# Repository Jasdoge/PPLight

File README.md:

# Usage:

1. The lamp automatically turns on when you move it
2. The lamp starts fading out after being still for 30 seconds, fully turning off after another 30 seconds.

## Charging:

1. Plug it to a 5V USB outlet with a Type-C cable.
2. The battery only charges at 100mA, so even a computer port will be able to charge it.
3. While charging, the lights will fade in and out with a pause between.
4. When fully charged, the lights will turn off.
5. A fully discharged battery reaches 90%+ charge in 2 hours.

## Troubleshooting:

1. After charging, you may need to led the device be still for a few seconds before it can turn on again.
2. If the device still won't turn on, you may need to reset it (this should be exceedingly rare though, and I didn't manage to reproduce it myself after setting the proper BOD). To reset it, open the case by removing the lid (but be careful since the silk filament is a little brittle), and use a fork or knife to briefly short the BAT1 solder joints.

# 3d printing

The 3d print files are located in the Prints director. It's designed for a multi material printer where you want to combine the lid and logo into one mesh, giving the logo priority.

# Schematics

Schematics are located within the Kicad directory.

# Reprogramming

If you want to reprogram your light you'll need the following:

- An arduino (pref arduino UNO)
- A breadboard
- A 10uF electrolytic capacitor
- A 4.7 kOhm resistor.
- 8-pin SOIC test clips. https://www.aliexpress.com/item/33058340727.html

1. Install the MegaTinyCore library in arduino. (If you haven't installed Arduino, do so at https://www.arduino.cc/
2. Then follow the instructions here: https://github.com/SpenceKonde/megaTinyCore/blob/master/MakeUPDIProgrammer.md But **do not connect the power pin to the PPLight**. In the tutorial they use a 470 ohm resistor on the UPDI wire, you can use a 4.7k instead, it doesn't matter that much.
3. Connect pin 6 of your arduino to your breadboard, then to pin 6 of the clips (second from the bottom right, the red wire on the clips is top left).
4. Connect ground to the top right of your test clips.
5. Connect the clips to the attiny on the board. The chamfered edge is left. Align it so the red cable on the clips is top left.
6. Use the following arduino settings:
- Board: ATtiny412/402/212/202
- Chip: ATtiny402
- Clock: 1 MHz internal
- millis()/micros(): Enabled (default timer)
- Support SerialEvent: No
- Port: Port of your arduino
- Programmer: jtag2updi
- The rest don't matter. Don't burn bootloader unless you know what you're doing.
7. You should now be able to upload your code.

**Note: If you're struggling with these instructions, let me know and I'll make a youtube video**

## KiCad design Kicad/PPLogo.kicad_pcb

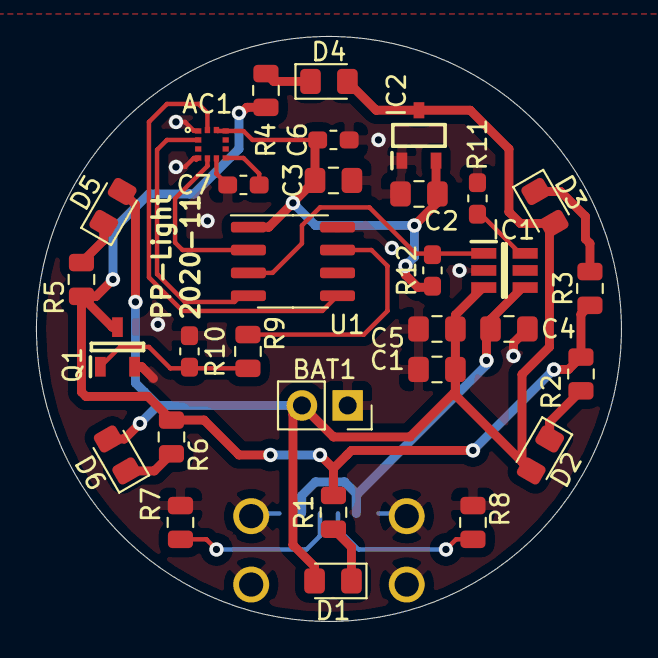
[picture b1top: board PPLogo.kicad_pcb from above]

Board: 2 copper layers, 32.5 x 32.5 mm, 32 parts (1 on the bottom side), 21 nets.

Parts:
AC1: KXTJ3-1057; 2X2X0.9MMLGA
BAT1: BAT; PinSocket_1x02_P2.54mm_Vertical
C1, C2, C3, C4, C5: 10uF; C_0805_2012Metric_Pad1.15x1.40mm_HandSolder
C6, C7: 0.1uF; C_0603_1608Metric_Pad1.05x0.95mm_HandSolder
D1, D2, D3, D4, D5, D6: LED; LED_0805_2012Metric_Pad1.15x1.40mm_HandSolder
IC1: TP4057-42-SOT26-R; SOT95P280X125-6N
IC2: XC6206P332MR; SOT95P280X130-3N
J1: TYPE-C-31-M-17; TYPEC31M17
Q1: JST2302H; SOT95P240X115-3N
R1, R2, R3, R4, R5, R6: 220; R_0805_2012Metric
R7, R8: 5.1k; R_0805_2012Metric
R9: 10; R_0805_2012Metric
R10, R11, R12: 10k; R_0603_1608Metric_Pad1.05x0.95mm_HandSolder
U1: ATtiny402-SS; SOIC-8_3.9x4.9mm_P1.27mm

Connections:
/3v3: AC1.10, AC1.11, C2.2, C3.1, C6.1, IC2.2, R12.1, U1.1
/3v7-5v: BAT1.2, C1.2, C5.1, D1.2, D2.2, D3.2, D4.2, D5.2, D6.2, IC1.3, IC2.3
/USB_V: C4.2, IC1.4, J1.A9, J1.B9
CHRG: IC1.1, R12.2, U1.3
GND: AC1.1, AC1.4, AC1.6, BAT1.1, C1.1, C2.1, C3.2, C4.1, C5.2, C6.2, C7.2, IC1.2, IC2.1, J1.A12, J1.B12, J1.MH1, J1.MH2, J1.MH3, J1.MH4, Q1.2, R7.2, R8.2, R10.1, R11.1, U1.8
INT: AC1.5, U1.2
LED: R9.2, U1.7
unnamed: AC1.7, C7.1
unnamed: D1.1, R1.1
unnamed: D2.1, R2.1
unnamed: D3.1, R3.1
unnamed: D4.1, R4.1
unnamed: D5.1, R5.1
unnamed: D6.1, R6.1
unnamed: IC1.6, R11.2
unnamed: J1.A5, R8.1
unnamed: J1.B5, R7.1
unnamed: Q1.1, R9.1, R10.2
unnamed: Q1.3, R1.2, R2.2, R3.2, R4.2, R5.2, R6.2
SCL: AC1.12, U1.5
SDA: AC1.2, U1.4

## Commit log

2020-12-07 add code
2020-12-07 Add assets
2020-12-07 add schematic png
2020-12-09 lower brightness
2020-12-16 increase brightness & improve first boot
2021-01-05 Lowered brightness and duration to save battery
